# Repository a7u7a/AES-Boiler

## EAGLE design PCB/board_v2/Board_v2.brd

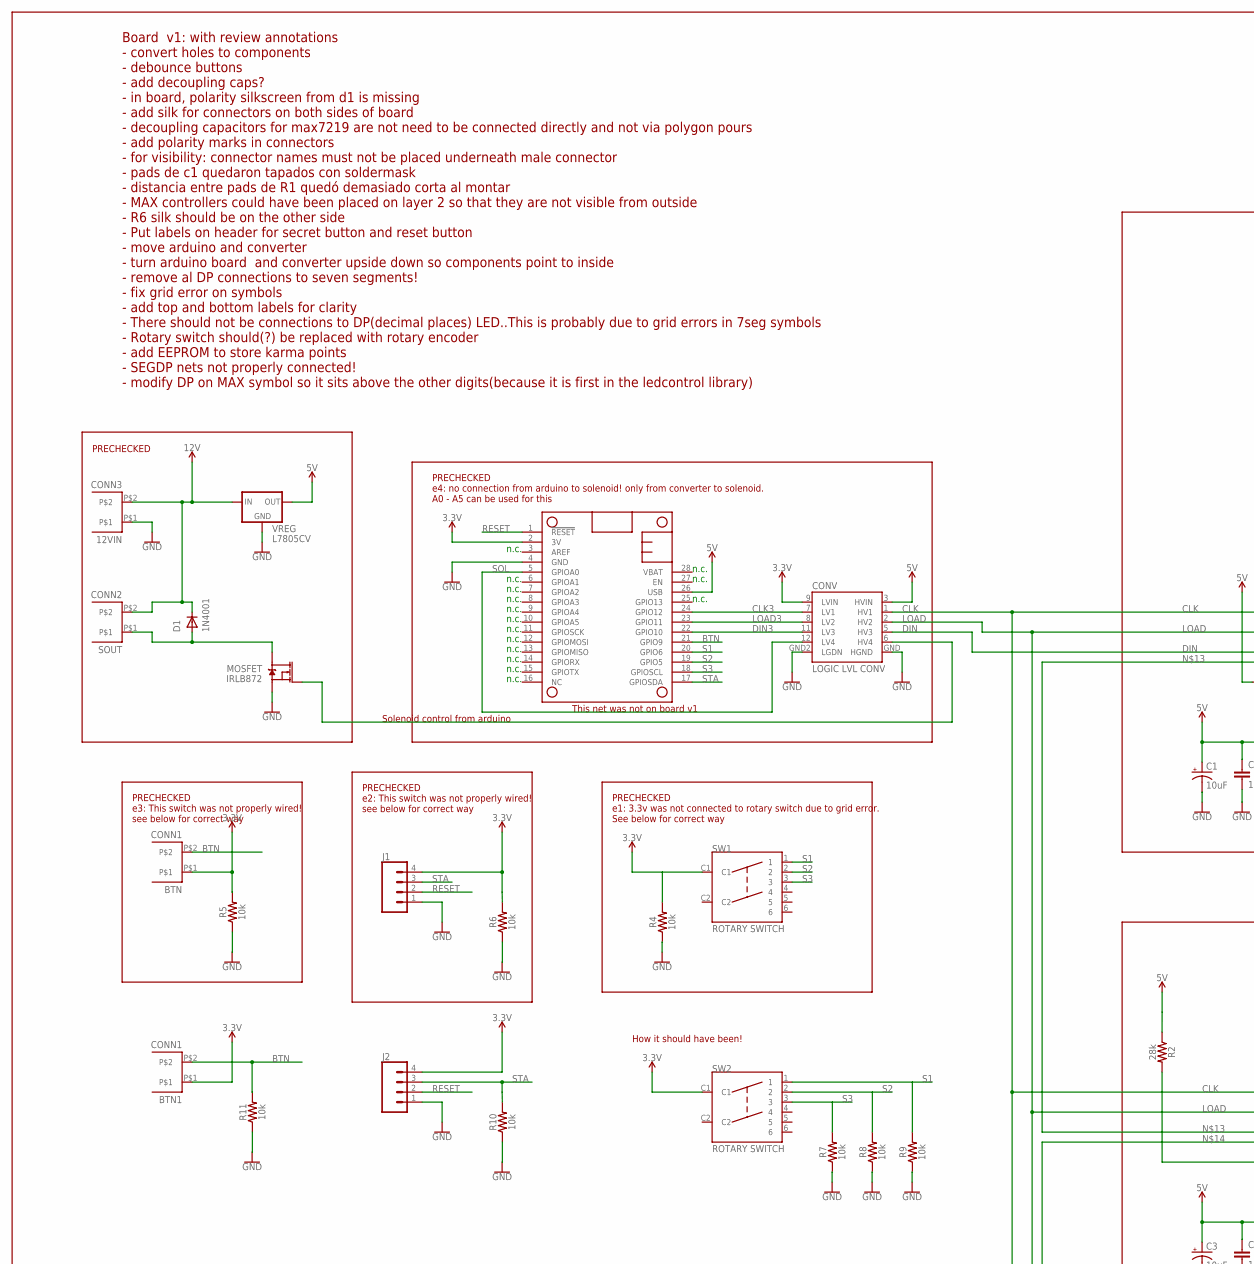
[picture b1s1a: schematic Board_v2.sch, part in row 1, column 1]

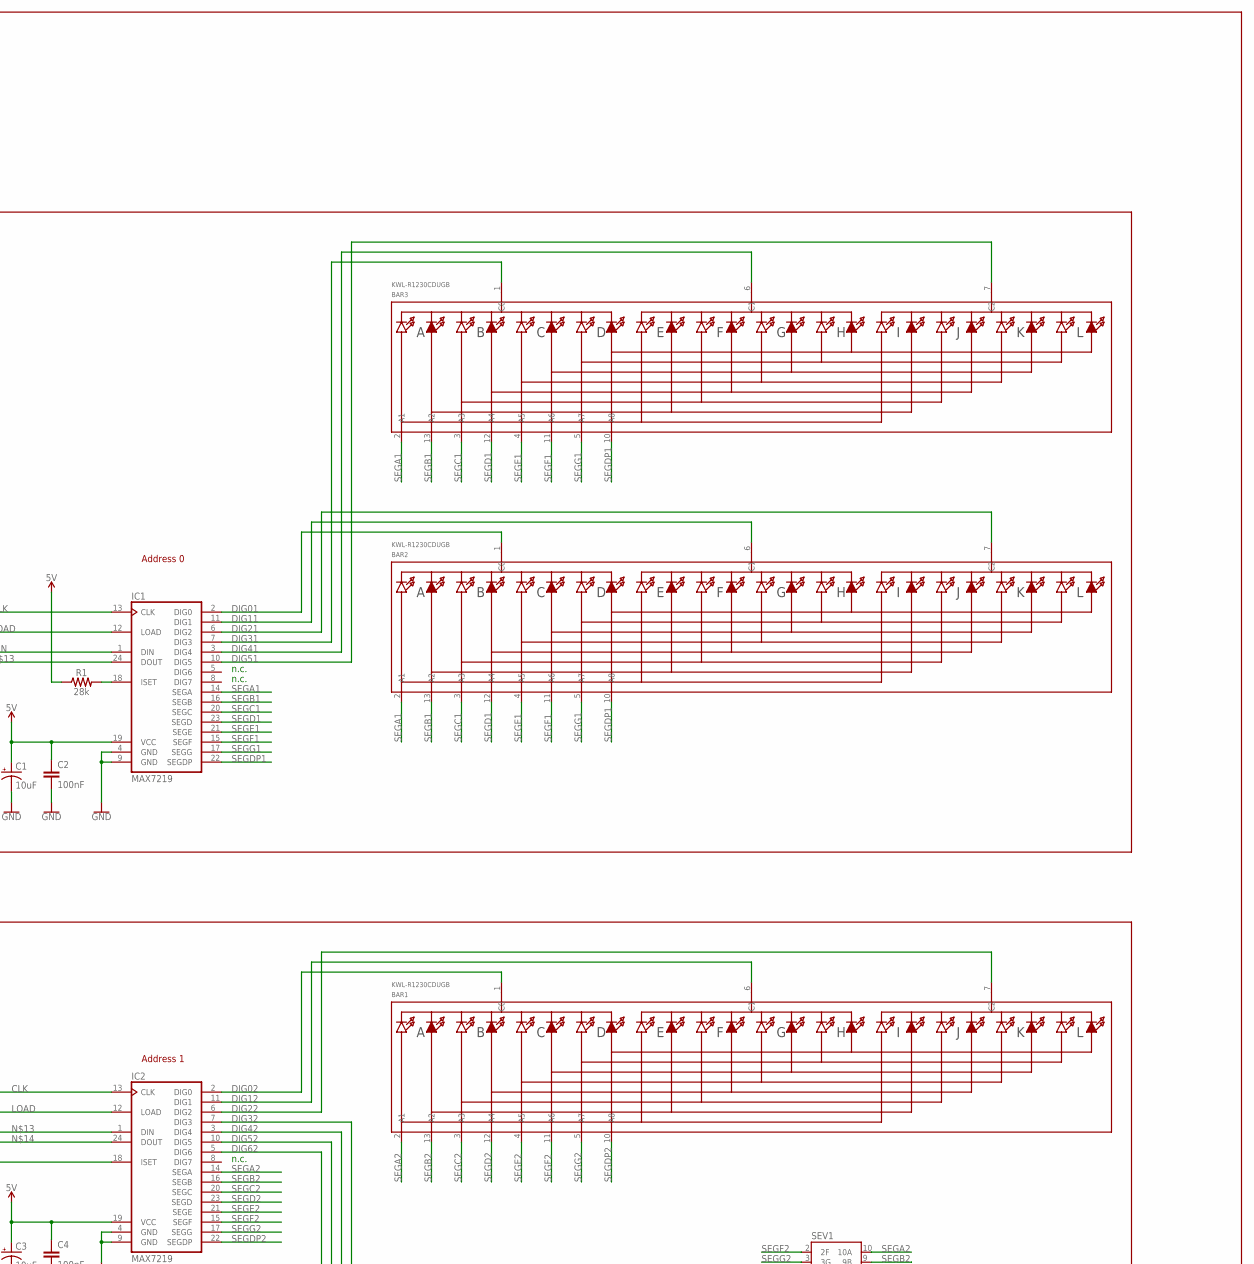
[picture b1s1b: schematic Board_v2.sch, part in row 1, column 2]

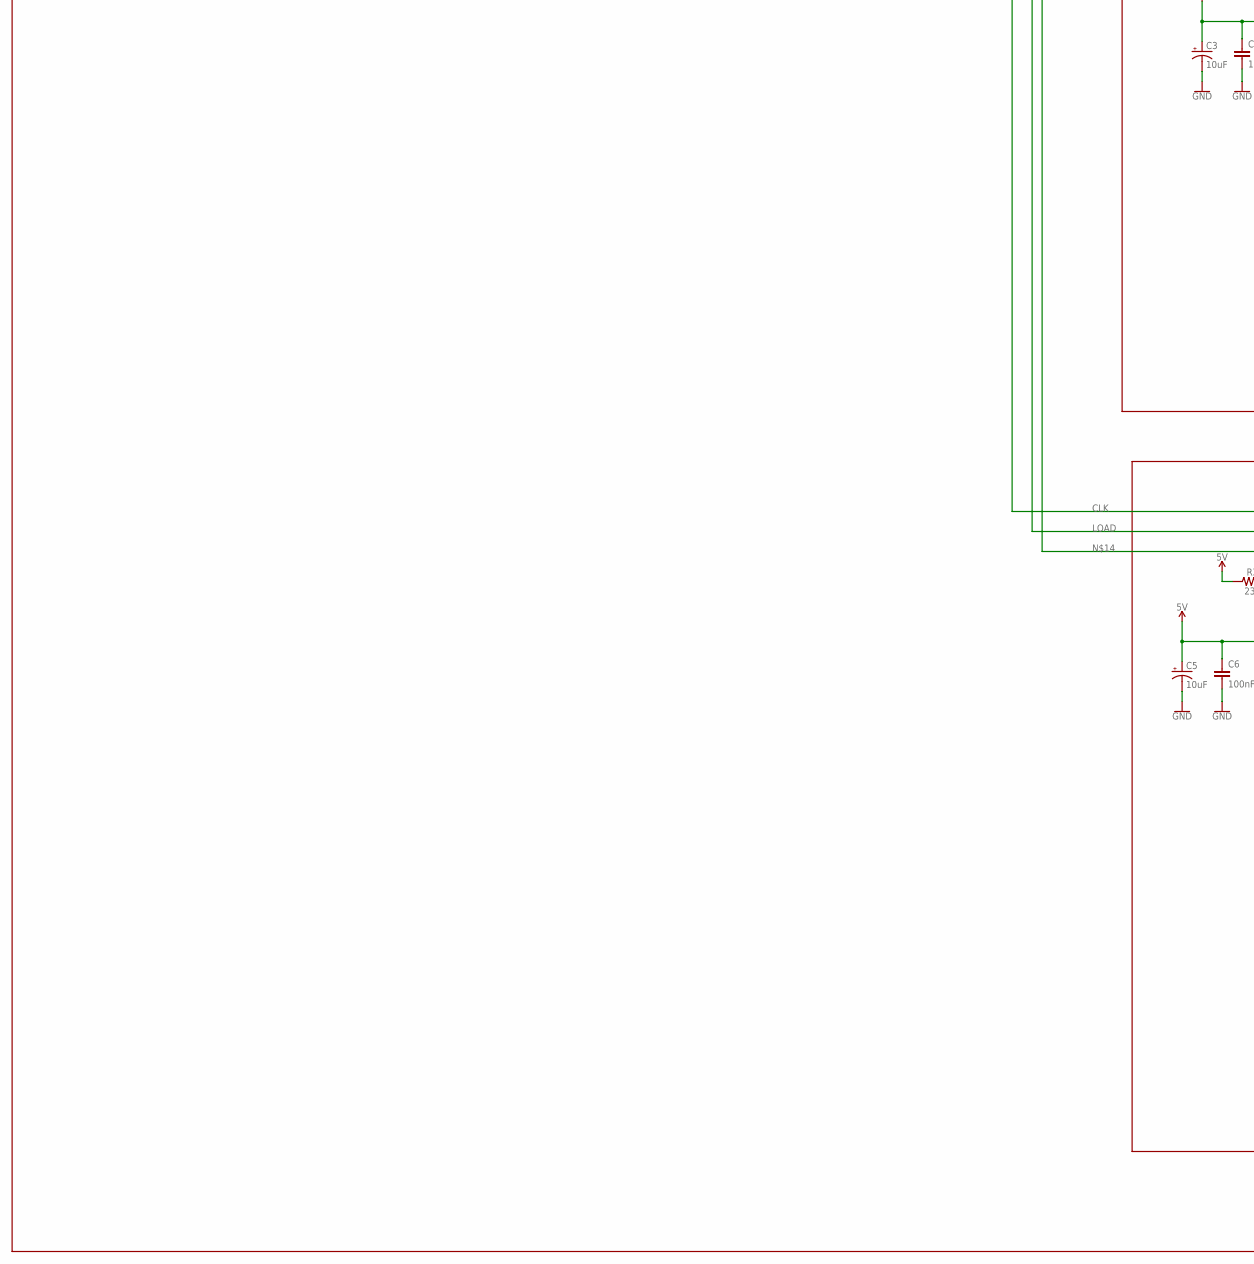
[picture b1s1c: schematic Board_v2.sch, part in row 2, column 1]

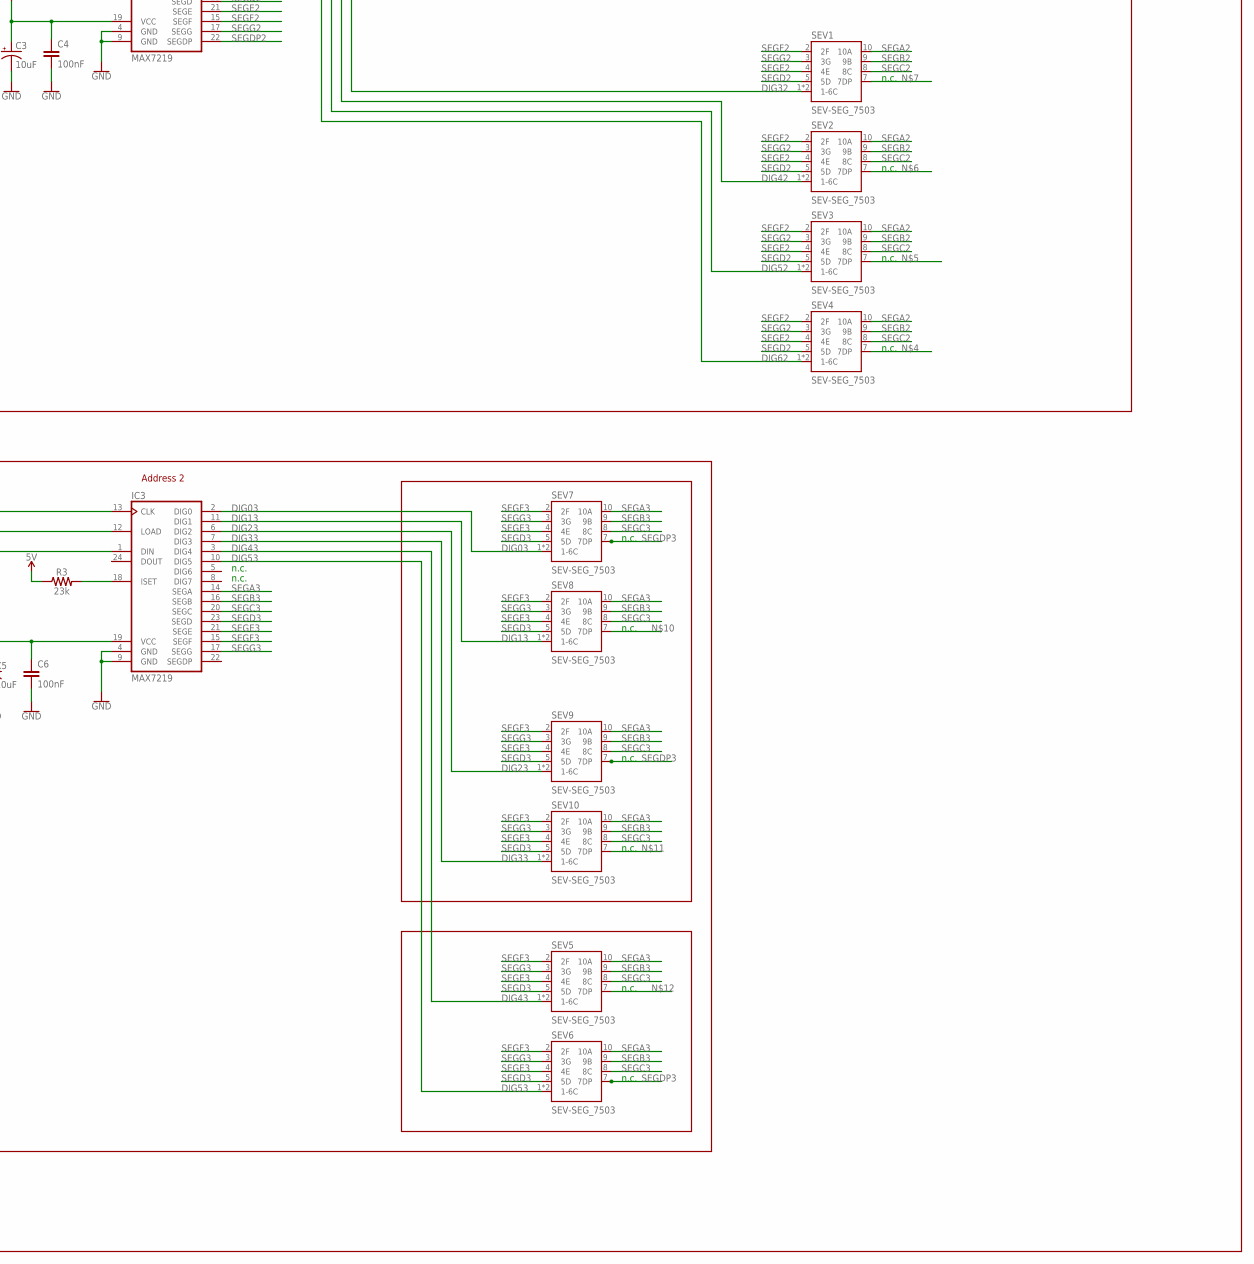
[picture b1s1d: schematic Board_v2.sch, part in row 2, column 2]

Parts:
12VIN: CONN3; MICRO-FIT_43560_3MM
BAR1, BAR2, BAR3: KWL-R1230CDUGB; SEGMENT_BICOL_BL-AR12Z3010
BTN, BTN1: CONN1; MICRO-FIT_43560_3MM
C1, C3, C5: 10uF; CPOL-RADIAL-2.5MM-5MM-KIT
C2, C4, C6: 100nF; CAP-PTH-5MM
CONV: LOGIC LVL CONV; 3-5V_LOGIC_LVL_CONV
D1: 1N4001; CASE59−10-AXIAL
FEATHERM0: FEATHERWING_NODIM; FEATHER
IC1, IC2, IC3: MAX7219; DIL24-3
J1, J2: CONN_041X04_NO_SILK; 1X04_NO_SILK
MOSFET: IRLB872; TO-220-ALT
R1, R2: 28k; AXIAL-0.3
R3: 23k; AXIAL-0.3
R4, R5, R6, R7, R8, R9, R10, R11: 10k; AXIAL-0.3
SEV1, SEV2, SEV3, SEV4, SEV5, SEV6, SEV7, SEV8, SEV9, SEV10: SEV-SEG_7503; HDSP-7503-C
SOUT: CONN2; MICRO-FIT_43560_3MM
SW1, SW2: ROTARY SWITCH; MRB24B_SP3T
VREG: L7805CV; TO-220-ALT

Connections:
3.3V: BTN.P$1, BTN1.P$1, CONV.9 (LVIN), FEATHERM0.2 (3V), J1.4, J2.4, R4.P$2 (2), R5.P$2 (2), R6.P$2 (2), SW1.C1, SW2.C1
5V: C1.1 (+), C2.1, C3.1 (+), C4.1, C5.1 (+), C6.1, CONV.3 (HVIN), FEATHERM0.26 (USB), IC1.19 (VCC), IC2.19 (VCC), IC3.19 (VCC), R1.P$1 (1), R2.P$1 (1), R3.P$1 (1), VREG.OUT
12V: 12VIN.P$2, D1.CAT (C), SOUT.P$2, VREG.IN
BTN: BTN.P$2, BTN1.P$2, FEATHERM0.21 (GPIO9), R11.P$2 (2)
CLK: CONV.1 (HV1), IC1.13 (CLK), IC2.13 (CLK), IC3.13 (CLK)
CLK3: CONV.7 (LV1), FEATHERM0.24 (GPIO12)
DIG01: BAR2.1 (C0), IC1.2 (DIG0)
DIG02: BAR1.1 (C0), IC2.2 (DIG0)
DIG03: IC3.2 (DIG0), SEV7.1 (1-6C), SEV7.6 (1-6C)
DIG11: BAR2.6 (C1), IC1.11 (DIG1)
DIG12: BAR1.6 (C1), IC2.11 (DIG1)
DIG13: IC3.11 (DIG1), SEV8.1 (1-6C), SEV8.6 (1-6C)
DIG21: BAR2.7 (C2), IC1.6 (DIG2)
DIG22: BAR1.7 (C2), IC2.6 (DIG2)
DIG23: IC3.6 (DIG2), SEV9.1 (1-6C), SEV9.6 (1-6C)
DIG31: BAR3.1 (C0), IC1.7 (DIG3)
DIG32: IC2.7 (DIG3), SEV1.1 (1-6C), SEV1.6 (1-6C)
DIG33: IC3.7 (DIG3), SEV10.1 (1-6C), SEV10.6 (1-6C)
DIG41: BAR3.6 (C1), IC1.3 (DIG4)
DIG42: IC2.3 (DIG4), SEV2.1 (1-6C), SEV2.6 (1-6C)
DIG43: IC3.3 (DIG4), SEV5.1 (1-6C), SEV5.6 (1-6C)
DIG51: BAR3.7 (C2), IC1.10 (DIG5)
DIG52: IC2.10 (DIG5), SEV3.1 (1-6C), SEV3.6 (1-6C)
DIG53: IC3.10 (DIG5), SEV6.1 (1-6C), SEV6.6 (1-6C)
DIG62: IC2.5 (DIG6), SEV4.1 (1-6C), SEV4.6 (1-6C)
DIN: CONV.5 (HV3), IC1.1 (DIN)
DIN3: CONV.11 (LV3), FEATHERM0.22 (GPIO10)
GND: 12VIN.P$1, C1.2 (-), C2.2, C3.2 (-), C4.2, C5.2 (-), C6.2, CONV.GND (HGND), CONV.GND2 (LGDN), FEATHERM0.4 (GND), IC1.4 (GND), IC1.9 (GND), IC2.4 (GND), IC2.9 (GND), IC3.4 (GND), IC3.9 (GND), J1.1, J2.1, MOSFET.OUT (S), R4.P$1 (1), R5.P$1 (1), R6.P$1 (1), R7.P$1 (1), R8.P$1 (1), R9.P$1 (1), R10.P$1 (1), R11.P$1 (1), VREG.GND
LOAD: CONV.2 (HV2), IC1.12 (LOAD), IC2.12 (LOAD), IC3.12 (LOAD)
LOAD3: CONV.8 (LV2), FEATHERM0.23 (GPIO11)
unnamed: IC1.18 (ISET), R1.P$2 (2)
unnamed: D1.ANOD (A), MOSFET.GND (D), SOUT.P$1
unnamed: CONV.6 (HV4), MOSFET.IN (G)
unnamed: IC3.18 (ISET), R3.P$2 (2)
unnamed: IC2.18 (ISET), R2.P$2 (2)
unnamed: IC1.24 (DOUT), IC2.1 (DIN)
unnamed: IC2.24 (DOUT), IC3.1 (DIN)
RESET: FEATHERM0.1 (!RESET), J1.2, J2.2
S1: FEATHERM0.20 (GPIO6), R9.P$2 (2), SW1.1, SW2.1
S2: FEATHERM0.19 (GPIO5), R8.P$2 (2), SW1.2, SW2.2
S3: FEATHERM0.18 (GPIOSCL), R7.P$2 (2), SW1.3, SW2.3
SEGA1: BAR2.2 (A1), BAR3.2 (A1), IC1.14 (SEGA)
SEGA2: BAR1.2 (A1), IC2.14 (SEGA), SEV1.10 (10A), SEV2.10 (10A), SEV3.10 (10A), SEV4.10 (10A)
SEGA3: IC3.14 (SEGA), SEV5.10 (10A), SEV6.10 (10A), SEV7.10 (10A), SEV8.10 (10A), SEV9.10 (10A), SEV10.10 (10A)
SEGB1: BAR2.13 (A2), BAR3.13 (A2), IC1.16 (SEGB)
SEGB2: BAR1.13 (A2), IC2.16 (SEGB), SEV1.9 (9B), SEV2.9 (9B), SEV3.9 (9B), SEV4.9 (9B)
SEGB3: IC3.16 (SEGB), SEV5.9 (9B), SEV6.9 (9B), SEV7.9 (9B), SEV8.9 (9B), SEV9.9 (9B), SEV10.9 (9B)
SEGC1: BAR2.3 (A3), BAR3.3 (A3), IC1.20 (SEGC)
SEGC2: BAR1.3 (A3), IC2.20 (SEGC), SEV1.8 (8C), SEV2.8 (8C), SEV3.8 (8C), SEV4.8 (8C)
SEGC3: IC3.20 (SEGC), SEV5.8 (8C), SEV6.8 (8C), SEV7.8 (8C), SEV8.8 (8C), SEV9.8 (8C), SEV10.8 (8C)
SEGD1: BAR2.12 (A4), BAR3.12 (A4), IC1.23 (SEGD)
SEGD2: BAR1.12 (A4), IC2.23 (SEGD), SEV1.5 (5D), SEV2.5 (5D), SEV3.5 (5D), SEV4.5 (5D)
SEGD3: IC3.23 (SEGD), SEV5.5 (5D), SEV6.5 (5D), SEV7.5 (5D), SEV8.5 (5D), SEV9.5 (5D), SEV10.5 (5D)
SEGDP1: BAR2.10 (A8), BAR3.10 (A8), IC1.22 (SEGDP)
SEGDP2: BAR1.10 (A8), IC2.22 (SEGDP)
SEGDP3: SEV6.7 (7DP), SEV7.7 (7DP), SEV9.7 (7DP)
SEGE1: BAR2.4 (A5), BAR3.4 (A5), IC1.21 (SEGE)
SEGE2: BAR1.4 (A5), IC2.21 (SEGE), SEV1.4 (4E), SEV2.4 (4E), SEV3.4 (4E), SEV4.4 (4E)
SEGE3: IC3.21 (SEGE), SEV5.4 (4E), SEV6.4 (4E), SEV7.4 (4E), SEV8.4 (4E), SEV9.4 (4E), SEV10.4 (4E)
SEGF1: BAR2.11 (A6), BAR3.11 (A6), IC1.15 (SEGF)
SEGF2: BAR1.11 (A6), IC2.15 (SEGF), SEV1.2 (2F), SEV2.2 (2F), SEV3.2 (2F), SEV4.2 (2F)
SEGF3: IC3.15 (SEGF), SEV5.2 (2F), SEV6.2 (2F), SEV7.2 (2F), SEV8.2 (2F), SEV9.2 (2F), SEV10.2 (2F)
SEGG1: BAR2.5 (A7), BAR3.5 (A7), IC1.17 (SEGG)
SEGG2: BAR1.5 (A7), IC2.17 (SEGG), SEV1.3 (3G), SEV2.3 (3G), SEV3.3 (3G), SEV4.3 (3G)
SEGG3: IC3.17 (SEGG), SEV5.3 (3G), SEV6.3 (3G), SEV7.3 (3G), SEV8.3 (3G), SEV9.3 (3G), SEV10.3 (3G)
SOL: CONV.12 (LV4), FEATHERM0.5 (GPIOA0)
STA: FEATHERM0.17 (GPIOSDA), J1.3, J2.3, R10.P$2 (2)

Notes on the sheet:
n.c.
PRECHECKED e1: 3.3v was not connected to rotary switch due to grid error. See below for correct way
Board v1: with review annotations - convert holes to components - debounce buttons - add decoupling caps? - in board, polarity silkscreen from d1 is missing - add silk for connectors on both sides of board - decoupling capacitors for max7219 are not need to be connected directly and not via polygon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
PRECHECKED e2: This switch was not properly wired! see below for correct way
PRECHECKED
Solenoid control from arduino
PRECHECKED e4: no connection from arduino to solenoid! only from converter to solenoid. A0 - A5 can be used for this
How it should have been!
PRECHECKED e3: This switch was not properly wired! see below for correct way
This net was not on board v1
Address 0
Address 1
Address 2

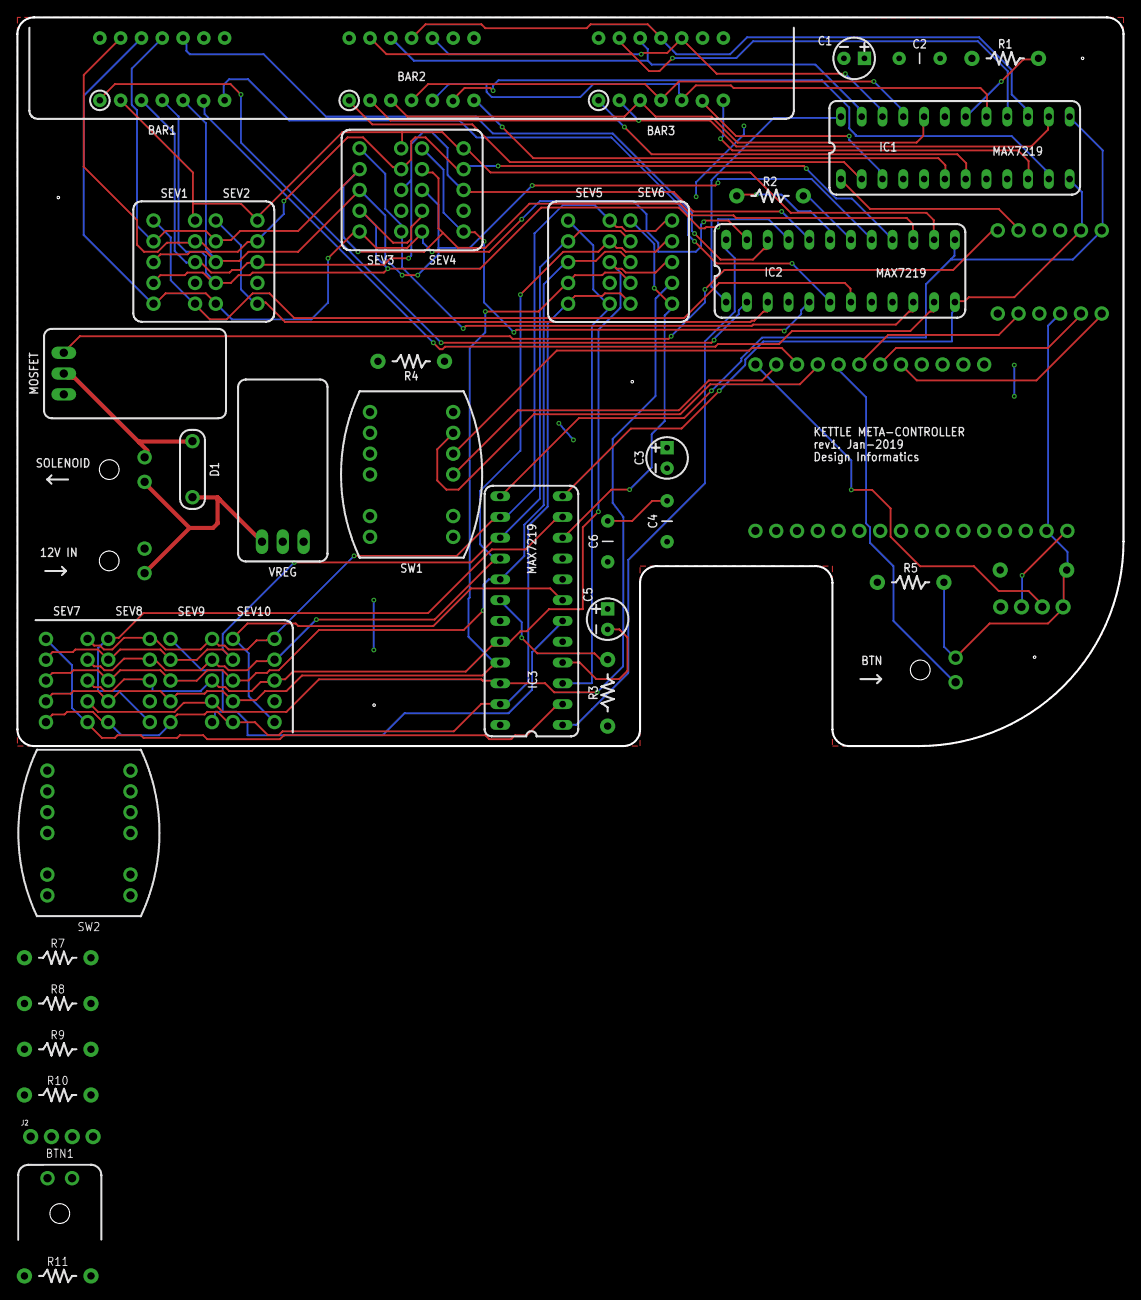
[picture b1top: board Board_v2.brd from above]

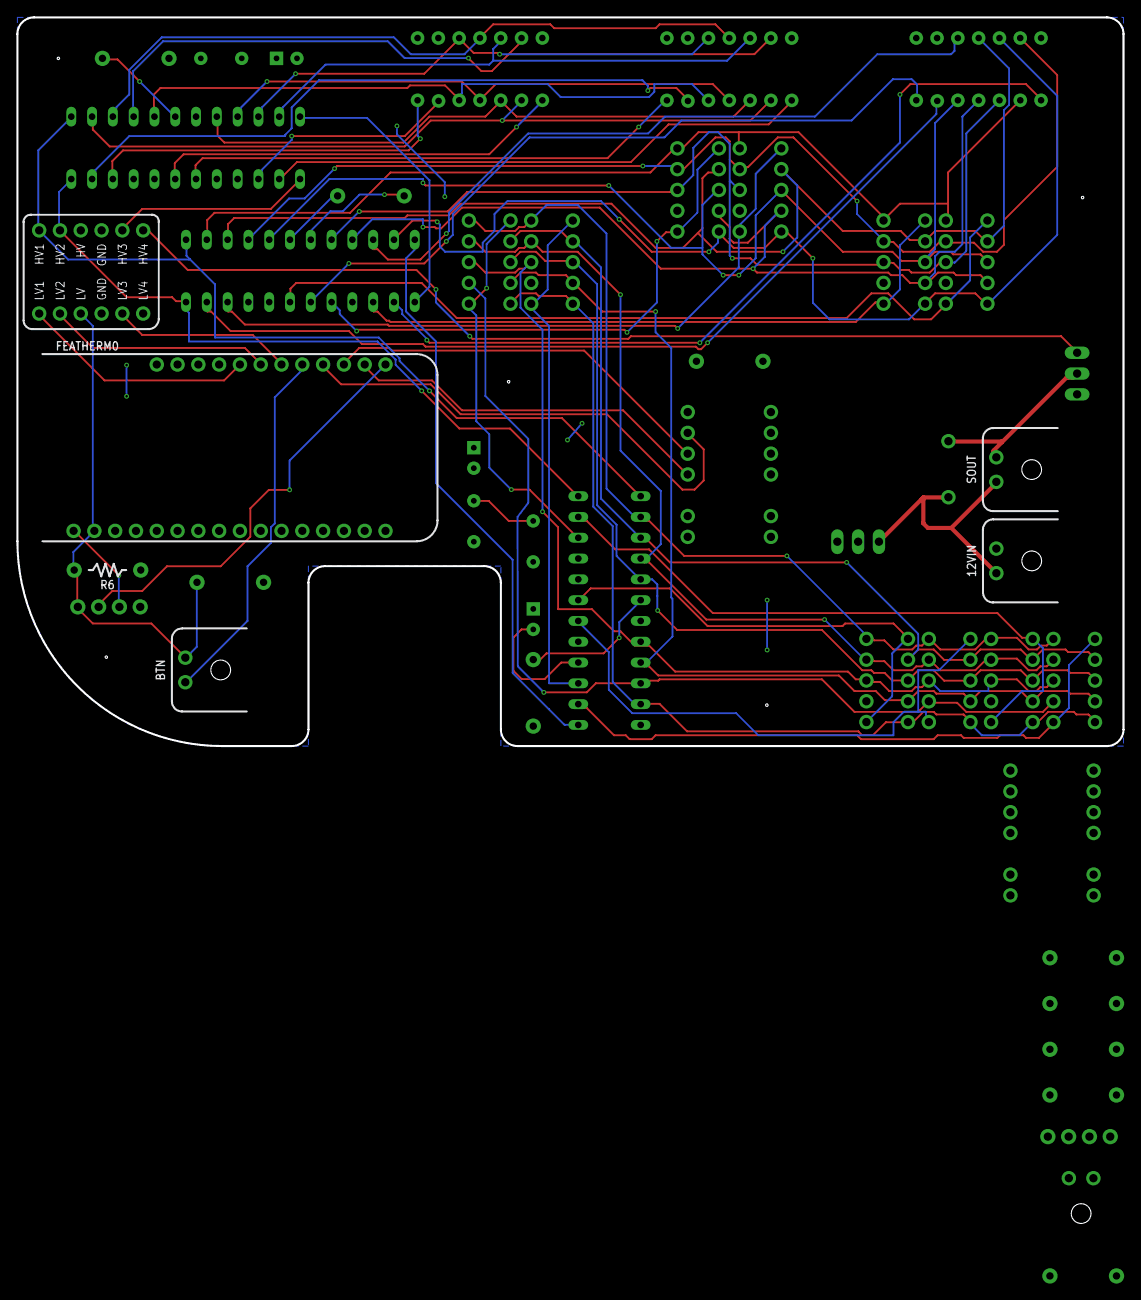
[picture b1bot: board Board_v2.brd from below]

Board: 2 copper layers, 135.1 x 89.0 mm, 46 parts (6 on the bottom side), 67 nets.

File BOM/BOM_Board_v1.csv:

"Qty";"Value";"Device";"Package";"Parts";"Description";"MF";"MPN";"OC_FARNELL";"OC_NEWARK";"PROD_ID";
"1";"";"CONN_041X04_NO_SILK";"1X04_NO_SILK";"J1";"Multi connection point. Often used as Generic Header-pin footprint for 0.1 inch spaced/style header connections";"";"";"";"";"CONN-09696";
"3";"100nF";"CAP_CERAMIC";"CAP-PTH-5MM";"C2, C4, C6";"";"";"";"";"";"";
"3";"10k";"RESISTOR";"AXIAL-0.3";"R4, R5, R6";"";"";"";"";"";"";
"3";"10uF";"CAP_POL";"CPOL-RADIAL-2.5MM-5MM-KIT";"C1, C3, C5";"";"";"";"";"";"";
"1";"1N4001";"1N4001";"CASE59−10-AXIAL";"D1";"";"";"";"";"";"";
"1";"23k";"RESISTOR";"AXIAL-0.3";"R3";"";"";"";"";"";"";
"2";"28k";"RESISTOR";"AXIAL-0.3";"R1, R2";"";"";"";"";"";"";
"1";"CONN1";"MICRO-FIT_3.0_43650";"MICRO-FIT_43560_3MM";"BTN";"";"";"";"";"";"";
"1";"CONN2";"MICRO-FIT_3.0_43650";"MICRO-FIT_43560_3MM";"SOUT";"";"";"";"";"";"";
"1";"CONN3";"MICRO-FIT_3.0_43650";"MICRO-FIT_43560_3MM";"12VIN";"";"";"";"";"";"";
"1";"FEATHERWING_NODIM";"FEATHERWING_NODIM";"FEATHER";"FEATHERM0";"";"";"";"";"";"";
"1";"IRLB872";"IRLB872";"TO-220-ALT";"MOSFET";"";"";"";"";"";"";
"3";"KWL-R1230CDUGB";"KWL-R1230CDUGB";"SEGMENT_BICOL_BL-AR12Z3010";"BAR1, BAR2, BAR3";"";"";"";"";"";"";
"1";"L7805CV";"L7805CV";"TO-220-ALT";"VREG";"";"";"";"";"";"";
"1";"LOGIC LVL CONV";"3-5V_LOGIC_LVL_CONV";"3-5V_LOGIC_LVL_CONV";"CONV";"";"";"";"";"";"";
"3";"MAX7219";"MAX7219CNG";"DIL24-3";"IC1, IC2, IC3";"LED DISPLAY DRIVER";"MAXIM";"MAX7219CNG";"1523914";"34C4018";"";
"1";"ROTARY SWITCH";"MRB_ROTARY_SWITCH";"MRB24B_SP3T";"SW1";"";"";"";"";"";"";
"10";"SEV-SEG_7503";"SEV-SEG_7503";"HDSP-7503-C";"SEV1, SEV2, SEV3, SEV4, SEV5, SEV6, SEV7, SEV8, SEV9, SEV10";"";"";"";"";"";"";

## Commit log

2018-12-11 added arduino code
2018-12-11 PCB v1 WIP
2018-12-12 added button pcb
2018-12-12 ready to start routing?
2018-12-12 routing v1 finish
2018-12-13 ready for fabhouse v1
2018-12-13 added CAM files for button board
2019-01-04 added board v2 files with annotations from board v1
2019-01-07 added precheck marks on board-v2
2019-01-07 more corrections to board v2: new rotary switch connection in schematic
2019-01-08 added 'mfg_image'
2019-01-08 more pull down updates
2019-01-09 new annotations to boardv2 files
2019-01-09 boardv2 files annotated with new found errors
2019-01-09 renamed 'Firmware' folder to 'AES_Boiler_Firmware'
2019-01-09 started vscode project
2019-01-10 started working on firmware, initial versions of full power test
2019-01-10 working version of full power test
2019-01-10 added first attempt at digits and bars abstraction
2019-01-10 selector leds working with rotary switch
2019-01-11 added fade test sketch
2019-01-11 more annotations to eagle file board_v2
2019-01-14 changed code folder to src, preparing to separate pcb and code into separate repos. added interrupt_test1.ino
2019-01-14 functional version of bars_displayval.ino
2019-01-15 added bars_function_test.ino
2019-01-15 working version of bars_function_test.ino
2019-01-15 added bars_function_test2.ino
2019-01-16 updated bars_function_test2.ino, added bars_function_test3.ino
2019-01-16 rearragned folders
2019-01-16 usable version of displayBar and modBar in bars_function_test3.ino
2019-01-16 usable version of displayBar + modBar + modBlink in bars_function_test3.ino
2019-01-16 added loop_test1.ino for testing the complete interaction
2019-01-16 working version of loop_test1.ino
2019-01-16 working fade in and fade out to loop_test1.ino
2019-01-16 added while_btn_rotaryswitch.ino to test while condition
2019-01-18 added solenoid control to boil water
2019-01-18 added gridChange_v1.ino to test timer on state change
2019-01-18 gridChange_v1.ino apparently ready to be merged into loop_test1.ino
2019-01-18 interrupt for state change test
2019-01-19 loop_test1.ino as used in BRE, added bug mode files
2019-01-19 bugMode update
2019-01-20 progress on longpress version
2019-01-22 updated pcbv2

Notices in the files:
parts and their libraries:
SparkFun-Connectors: Licensing: Creative Commons ShareAlike 4.0 International - https://creativecommons.org/licenses/by-sa/4.0
